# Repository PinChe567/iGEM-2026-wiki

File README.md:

# AeroSense Wiki

The workspace intentionally keeps two website directories. Edit and preview in `aerosense-wiki/`. At a chosen milestone, copy the website contents into `github/iGEM-2026-wiki/`, preserving that repository's `.git` directory. Commit and push from the GitHub copy, which connects to `https://github.com/PinChe567/iGEM-2026-wiki.git` on branch `main`. These two directories are required working copies; do not remove either during duplicate-file cleanup or synchronize them automatically. The separate workspace-level `zenodo-release/` contains research documents, code and original data and is not part of the website copy.

## Preview and editable sources

This GitHub copy supports English and Traditional Chinese. Run `node scripts/preview-server.mjs 8017` here; `preview.ps1` is also available. Every main Wiki page, learning dashboard, parameter viewer and current educational game has a language control. English remains the default. Selecting a language is remembered across navigation, reloads and the games; switching still works when browser storage is unavailable. The separate daily-editing and official GitLab copies remain unchanged and English-only.

English HTML remains the authoritative content. The local translation runtime changes display text without replacing scientific data, links or page state. Bibliographic records, identifiers and original image/PDF/download contents retain their recorded language. Chinese text for current scientific updates is editable in `locales/github-updates.zh-Hant.json`; retained page catalogs live under `locales/`.

After editing translations run `python scripts/build-locales.py`, then `python scripts/build-locales.py --check` and `node scripts/build-home-bundles.mjs`. After game changes run `npm --prefix game run build:wiki`. Do not copy this bilingual interface back into `aerosense-wiki/` or `gitlab/nthu/`. A future authorized source sync must preserve or deliberately reapply this GitHub-only localization. This copy was updated on 2026-11-03 without committing, pushing or deploying.

Run `node scripts/build-home-bundles.mjs` after editing homepage sources listed in `home-bundle-sources.json`. Keep the source inputs and their browser bundles.

Keep `game/apps/wiki-client/dist/`: the website uses this playable build. Reinstall game dependencies from its package manifests and lockfile only when rebuilding; do not commit `node_modules`.

## Media and research availability

Verified images, fonts, models, documents and microscopy frame data load from official iGEM URLs. The canonical records are `igem-upload/verified-official-urls.json` and `igem-upload/official-upload-receipt.json`. No local video file is a website runtime dependency. Scientific originals and publication video exports remain in the research package.

The Education and Sustainability pages retain the supplied source content, numerical results, tables and references. Education images and documents use official iGEM hosting. All five files from the linked Google Drive teacher toolkit were downloaded, retained in the local GitLab documentation package and linked through the official CDN. The resource upload receipt records 31 documents and figures with matching local and remote SHA-256 values. Notion and Google Drive were read only.

The Education Figure 1 is an original inline SVG activity map with eight linked regions, English labels and keyboard navigation. Edit it in `education.html` and `css/education.css`; the original Notion teaching image remains linked in the caption. No additional image build is required.

The three light-sheet recordings and the trypsin/benzamidine animation are publicly available on Video Universe. Anonymous readback also verified the other linked videos as Public and Published. The verification receipt is `audit/final-publication-20261021/video-readback.json`. Verified duplicate display copies have been removed; original AVI acquisitions and unique scientific outputs remain in the research package. Video playback time is not the acquisition clock.

The full research package remains unpublished in the separate `zenodo-release` directory. Selected code, documents and small supporting datasets are published through the official GitLab repository; eligible attachments use the official CDN. The previously supplied Zenodo DOI returned HTTP 404 and is being replaced by specific available files or the explicit archive-status document. Add a Zenodo DOI only after public publication and verification. Do not recreate research-download copies inside this website.

The two interactive parameter viewers remain local because they run on the website. Original CAD/STL files are in the research package. `node scripts/build_hardware_web_model.mjs` finds the workspace-level `zenodo-release/aerosense-wiki` from either website directory, or reads `AEROSENSE_RESEARCH_ROOT` when set.

## Publication

The official publication checkout is `../gitlab/nthu/`, separate from the intentionally preserved GitHub staging copy. Its CI builds the editable English website, shared design system and educational game from source; compiled deployment output is not committed. Synchronization and publication require the user's instruction. Never copy or remove its `.git` directory. The local site remains the daily editing source.

Run these commands from this directory:

1. `node scripts/audit-publish-assets-v7.cjs`
2. `python scripts/prepare_publication_manifest_v7.py`
3. Only when a deployment output is actually needed: `python scripts/build-publication.py`

The first two update existing metadata without copying the website. The third creates a `public` deployment directory. These commands do not upload HTML or push a repository. Keep only one current deployment output when needed.

`publication-files.json` lists website dependencies. See `scripts/PUBLICATION.txt` for preparation details. Root and site ignore rules exclude research packages, dependency caches and temporary outputs from website commits.

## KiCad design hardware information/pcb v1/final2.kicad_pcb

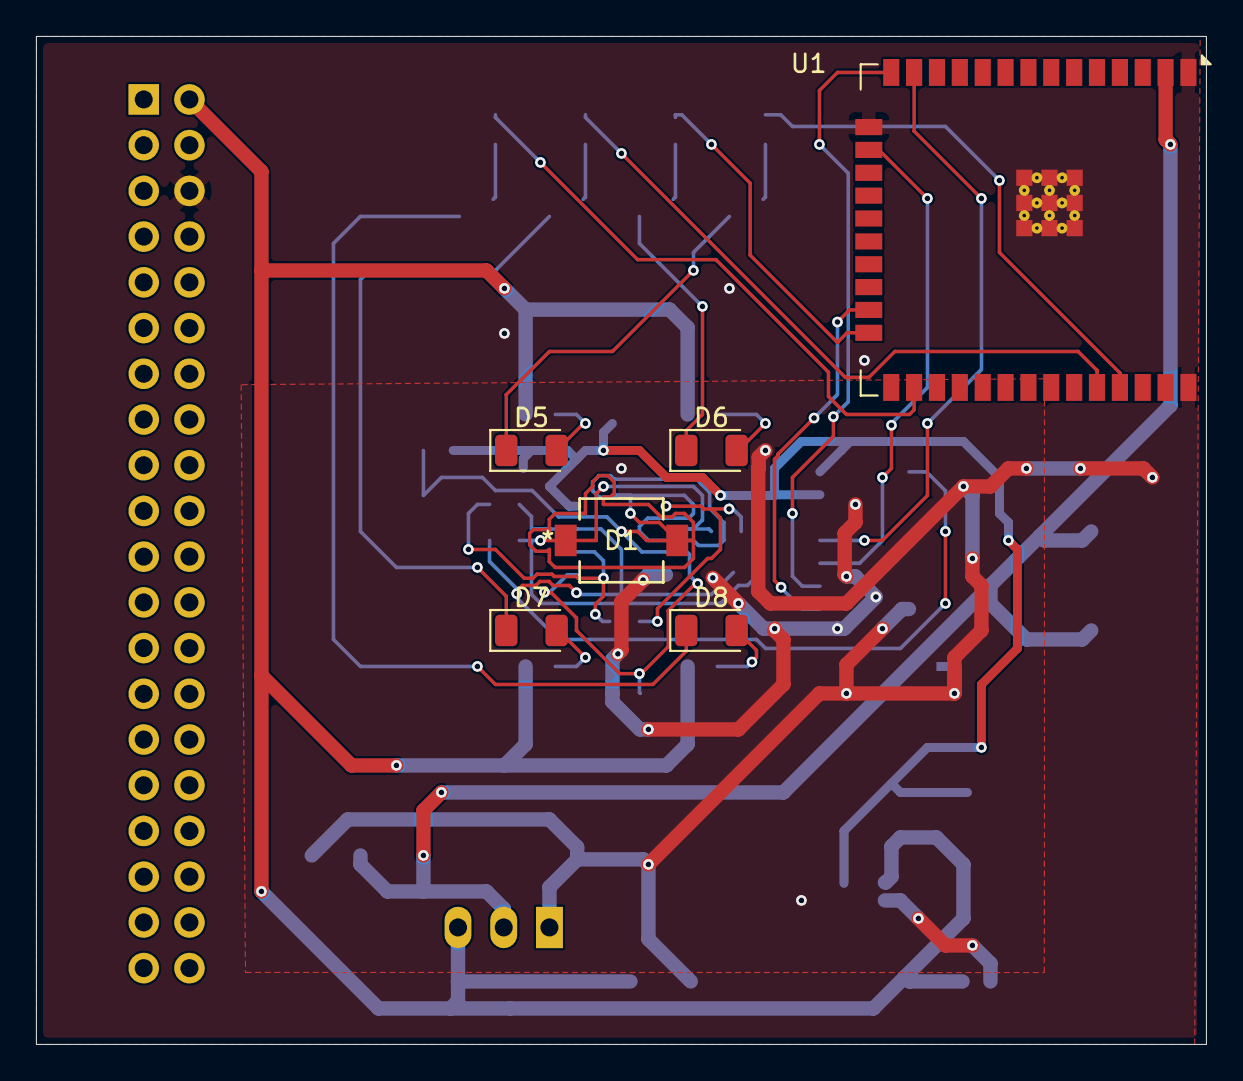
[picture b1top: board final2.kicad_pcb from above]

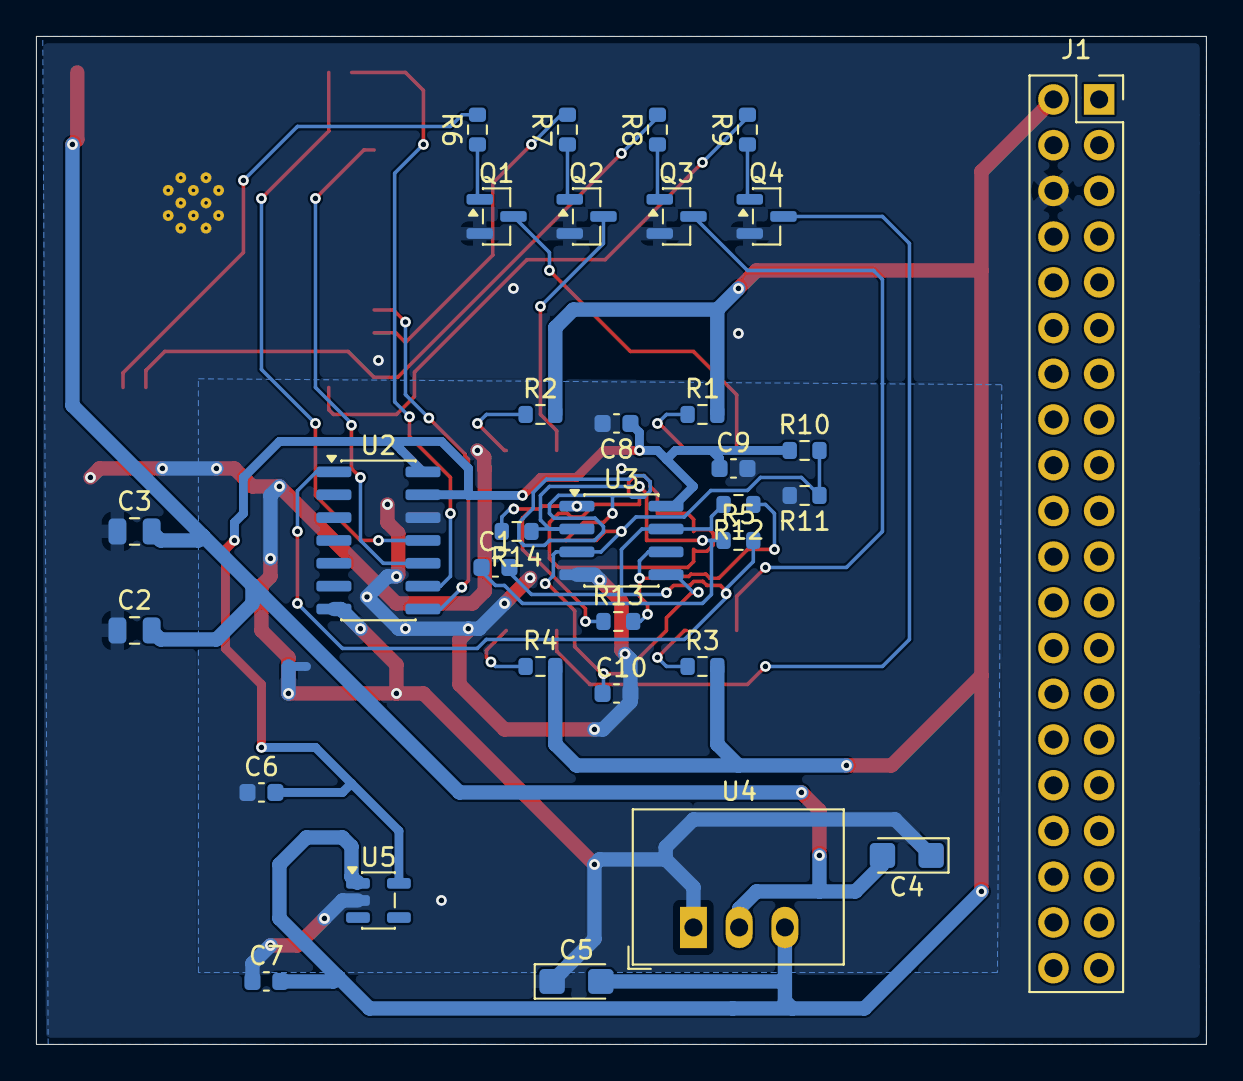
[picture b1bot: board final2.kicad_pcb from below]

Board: 2 copper layers, 65.0 x 56.0 mm, 40 parts (34 on the bottom side), 30 nets.

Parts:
C1, C6, C7, C8, C9, C10: C_Small; C_0603_1608Metric
C2, C3: C_Small; C_0805_2012Metric
C4, C5: C_Small; CP_EIA-3216-18_Kemet-A
D1: D_Photo; LED_VBPW34S_VIS
D5, D6, D7, D8: LED; LED_1206_3216Metric
J1: Conn_02x20_Odd_Even; PinSocket_2x20_P2.54mm_Vertical
NT1: NetTie_2; NetTie-2_SMD_Pad0.5mm
Q1, Q2, Q3, Q4: AO3400A; SOT-23
R1, R2, R3, R4: R_Small_47R; R_0603_1608Metric
R5: R_Small_10MR; R_0603_1608Metric
R6, R7, R8, R9, R10, R11, R12, R13, R14: R_Small; R_0603_1608Metric
U1: ESP32-WROOM-32E
U2: MCP3204; SOIC-14_3.9x8.7mm_P1.27mm
U3: LM358; SOIC-8_3.9x4.9mm_P1.27mm
U4: AMS1117CD-3.3; Converter_DCDC_RECOM_R-78E-0.5_THT
U5: LP5907MFX-3.3; SOT-23-5

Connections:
/1R: R13.1, R14.2, U3.1
/3.3V_ANA: C6.2, C8.1, C9.1, R10.1, U2.13 (Vref), U2.14 (Vdd), U3.8 (V+), U5.5 (OUT)
/3.3V_DIG: C2.2, C3.2, C4.2, U1.2 (VDD), U4.2 (VO)
/ADC_CH1_IN: C1.2, R5.2, R12.2, U2.1 (CH0), U3.7
/GND: C2.1, C3.1, C4.1, C5.1, J1.6, NT1.1, Q1.2 (S), Q2.2 (S), Q3.2 (S), Q4.2 (S), U1.1 (GND), U1.15 (GND), U1.38 (GND), U1.39 (GND), U2.7 (DGND), U4.1 (GND)
/GNDA: C6.1, C7.1, C8.2, C9.2, C10.2, NT1.2, R11.2, U2.12 (AGND), U3.4 (V-), U5.2 (GND)
/LEDA1: D5.1 (K), Q1.3 (D)
/LEDA2: D6.1 (K), Q2.3 (D)
/LEDA3: D7.1 (K), Q3.3 (D)
/LEDA4: D8.1 (K), Q4.3 (D)
/LEDC1: D5.2 (A), R1.1
/LEDC2: D6.2 (A), R2.1
/LEDC3: D7.2 (A), R3.1
/LEDC4: D8.2 (A), R4.1
/PD2TIA: C1.1, D1.1 (K), R5.1, R14.1, U3.2 (-)
/PWM_CH1I: R6.2, U1.35 (TXD0/IO1)
/PWM_CH1O: Q1.1 (G), R6.1
/PWM_CH2I: R7.2, U1.24 (IO2)
/PWM_CH2O: Q2.1 (G), R7.1
/PWM_CH3I: R8.2, U1.34 (RXD0/IO3)
/PWM_CH3O: Q3.1 (G), R8.1
/PWM_CH4I: R9.2, U1.26 (IO4)
/PWM_CH4O: Q4.1 (G), R9.1
/R6: R12.1, R13.2, U3.6 (-)
/SPI_CLK: U1.13 (IO14), U2.11 (CLK)
/SPI_CS: U1.23 (IO15), U2.8 (~CS/SHDN)
/SPI_MISO: U1.16 (IO13), U2.10 (Dout)
/SPI_MOSI: U1.14 (IO12), U2.9 (Din)
/USB_5V: C5.2, C7.2, J1.2, R1.2, R2.2, R3.2, R4.2, U4.3 (VI), U5.1 (IN)
/V_MID: C10.1, D1.2 (A), R10.2, R11.1, U3.3 (+), U3.5 (+)
